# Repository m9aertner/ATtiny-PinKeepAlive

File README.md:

# ATtiny-PinKeepAlive

Flash in the PIN for my utility electricity meter via white LED, then keep the PIN active by flashing the LED briefly every 100 seconds.

In parallel, read INFO-DSS SML datagrams via IR diode input, decode for a number of OBIS codes and expose the received values via Modbus RTU over a serial line, in my case RS-485.

# Why?

The electricity power meter supplied by my local power company came mis-configured so there's no way to enable extended INFO-DSS IR datagrams permanently.
The respective menu item has been configured away. Thank you very much!

After PIN entry, the extended datagrams do appear, but only for 120 seconds. After that, the unit falls back to basic datagrams again, requiring another PIN entry. Alternatively, we just simulate some activity so that the 120 second window does not close. By repeated light signals, we're keeping the unit in "extended" mode, so to say.

Without the PIN, my meter emits 1.8.0 and 2.8.0 with kWh resolution only (xxx000 W) and does not emit instantaneous power at all. After PIN entry, all three values are emitted and with Watt granularity.

# Manual operation

A button is connected to a small microcontroller (ATtiny841) and makes a LED light up when pressed. The button is de-bounced so that a minimum LED "on" duration of around half a second is maintained. The button can be pressed for longer, extending the "on" period, which enables entry of "long" press light impulses.

In short, this function converts the error-prone manual flashing contraption to simple button presses.

# Automatic PIN entry

Upon reset, the microcontroller enters austomatic mode. It remains in automatic mode unless the button is pressed.
In automatic mode, the unit first
- emits a short flash to enter the display test page (all display segments activated)
- emits another short flash to proceed to the PIN entry page. With my meter, the display's 2nd line now shows '-0...-' and waits for the first digit.

Then, for each of the (four) digits of the PIN,
- a sequence of short flashes, each followed by a brief OFF pause is emitted, according to the digit value.
- Between digits, we need a pause of about 3-4 seconds. The meter detects this inactivity and switches to the next PIN position automatically.

As we do not have any feedback from the meter (neither IR nor visual) we can do nothing but try and wait for a similar amount of time. Note this cannot be super reliable. If the period is set too short, we're bumping up the current digit too much and if we wait for too long we can skip a digit, causing one or more spurious 0 digits.

The PIN is hard-coded in the source code / microcontroller. To define the PIN, copy file `meterpin-sample.h` to `meterpin.h` and adjust that copy to your PIN. Then build and upload. Setting the PIN to an empty string disables PIN entry, leaving only the Modbus-RTU function, see below.

# Keep Alive

After the automatic PIN entry or the last button press, the unit waits for 100 seconds, then emits a half-second LED flash and repeats. Pressing the button interrupts this waiting period and causes an immediate flash.

This short flash once in a while simulates some activity to the power meter so it does not ever reach the 120 second (2 minute) PIN timeout.

Consequently, the extended SML datagrams continue to be emitted. Mission accomplished.

# Repeat PIN entry

One reviewer suggested to enter the PIN again, regularly, to guard against unexpected meter resets and/or unexpected microcontroller resets.
So, after about 20 minutes, the unit now waits for a bit longer than the keep-alive period (130s, extended wait period), then blinks in the PIN again.

# What the heck?

I still have not found the reason why anybody would want to configure away the option to emit extended datagrams permanently. What's the purpose?!

While my unit is an [Easymeter Q3A](https://www.easymeter.com/downloads/products/zaehler/Q3A/BA_Q3A_V10.09_Rev19_2021-06-14.pdf), I believe there may be other types of meters with similar (stupid?) config options.

# Modbus RTU Details

The unit's address is fixed to 0x09. Function code 0x04 (Read Input Registers) is the only function code supported.

Four values are exposed. Each value is a 32bit value, readable through two consecutive registers.

| Address  | Content                                            | Unit | Data type               |
|----------|----------------------------------------------------|------|-------------------------|
| 256, 257 | Version number                                     |      | 32 bit unsigned integer |
| 258, 259 | 1-0:1.8.0 Positive active energy (A+) total        | Wh   | 32 bit unsigned integer |
| 260, 261 | 1-0:2.8.0 Negative active energy (A+) total        | Wh   | 32 bit unsigned integer |
| 262, 263 | 1-0:16.7.0 Sum active instantaneous power (A+ - A-)| W    | 32 bit signed integer   |

Example readout using "modpoll" (https://www.modbusdriver.com/modpoll.html):

    modpoll -t 3:int -a 9 -0 -r 256 -c 4 -i -1 -b 115200 -s 2 COM6

    modpoll -t 3:hex -a 9 -0 -r 258 -c 6    -1 -b 115200 -s 2 COM6

The SML decoder accepts 64-bit raw values internally, but after application of the "scaler" it is expected that the resulting
value fits into 32 bits. Indeed my unit always uses an 8-octet fixed-length zero-padded integer representation for all measurement
values:

    07 01 00 01 08 00 FF                1–0:1.8.0
    62 1e                               Unit
    52 03                               Scaler 10^3
    59 00 00 00 01 18 CB 47 05          0x118CB4705 <=> 4710942469, scaled to 471094 Wh, displayed on the unit as 471 kWh

# Hardware Design

I've prepared the schematics and a PCB using [KiCad 8.0.2](https://www.kicad.org/). Find respective project files under the [kicad/](kicad/) folder:
* [kicad/PinKeepAlive.kicad_pcb](kicad/PinKeepAlive.kicad_pcb)
* [kicad/PinKeepAlive.kicad_sch](kicad/PinKeepAlive.kicad_sch)

# Notes

- None of the values are critical, I believe.
- Use a small 100nF blocking condensator as C5, and position that near the MCU
- In the power supply section, I used 47uF/16V for C3, C4 which I had lying around. For the VBUS that I use a rating of 16V suffices, but please adapt when you supply with a higher voltage.
- The infrared phototransistor L14G3 is __ancient__ and comes from my forgotten parts bin. See https://wiki.volkszaehler.org/howto/simpler_ir_leser for other devices that people have found to work OK.
- By way of connector J6, you can also add a normal UART SmartMeterReader (e.g. [Amazon](https://www.amazon.de/bitShake-SmartMeterReader-UART-IR-Lesekopf/dp/B09XRC6VYW)). That's how I have it running currently. No need to populate U2, R4, R5, Q2 in this case, of course.
- The RS485 module can be obtained from AliExpress, Ebay, Amazon, or https://www.makershop.de/module/kommunikation-module/ttl-rs485-adapter/
- Same for the AMS1117-3V3 module. The 3-pin variant can be soldered easily and allows VBUS of up to 15V: https://www.berrybase.de/step-down-converter-5v-3-3v/800ma-mit-pin-header
- For the very short RS485 cable that I use, no 120 Ohm termination resistor is required. For longer cable lengths, be sure to terminate the RS485 bus at either end, usually by closing a solder bridge on the RS485 module.

# Caveats

- The LED needs to cause a light stream of at least 400lux at the receiver. I found that a random LED flashlight that I "deconstructed" for the purpose worked nicely: Originally driven by 3x AAA, the LED seems to be OK with being driven by nearly 5V (at 100mA). I ended up using a constant-current circuit (http://www.loosweb.de/constant_current_sources/doc/en/index.html point 8) where the current is determined by the 50Ohms resistor (2x 100Ohms parallel is what I had). The flashing I get this way is strong enough for my meter.
- (Update) Now that my meter emits long datagrams without any further ado, I converted the LED part to a "heartbeat" by configuring away the PIN and setting a 60 second keep-alive interval. The main objective now is to use the RS485 portion.
- The timing of this whole PIN entry scheme is not overly critical, but certainly not fool-proof either. After all, it's intended for manual operation. Especially, the inter-digit delays may give you a problem. In this case, please adjust `DIGIT_GAP2_TICKS` in code and re-try.
- If your meter happens to __not__ have a sticker preventing access to the MSB-DSS (IR transmitter/receiver, lucky you!), you want to check there first, as the MSB-DSS may well emit extended datagrams irrspective of PIN entry status - that is, even without a PIN!
- Why ATtiny841? Well, that was the nearest unit I happened to find on my workbench. And it's got two hardware serial ports, which I use now to read the SML and forward that via wired RS485. Of course, for the basic LED flash function any Arduino-like microcontroller
with some form of periodic interrupt should work.
- Note that during the last seconds of the extended wait period, plus the seconds it takes to re-enter the PIN, the meter will send out reduced datagrams again. Please ping me when you know a way around this.
- Please note that Modbus-RTU **requires** eleven bit times per character on the line. This means that when __not__ using any parity one must use **two** stop bits (start bit, 8 character bits, 2 stop bits == 11 bits). While some tools worked with just one stop bit  (modpoll), I found that others do not! Yes, especially PyModbus did rightfully **not** work unless the unit was configured to two stop bits. And that's critical as my HomeAssistant Modbus integration uses PyModbus under the covers.

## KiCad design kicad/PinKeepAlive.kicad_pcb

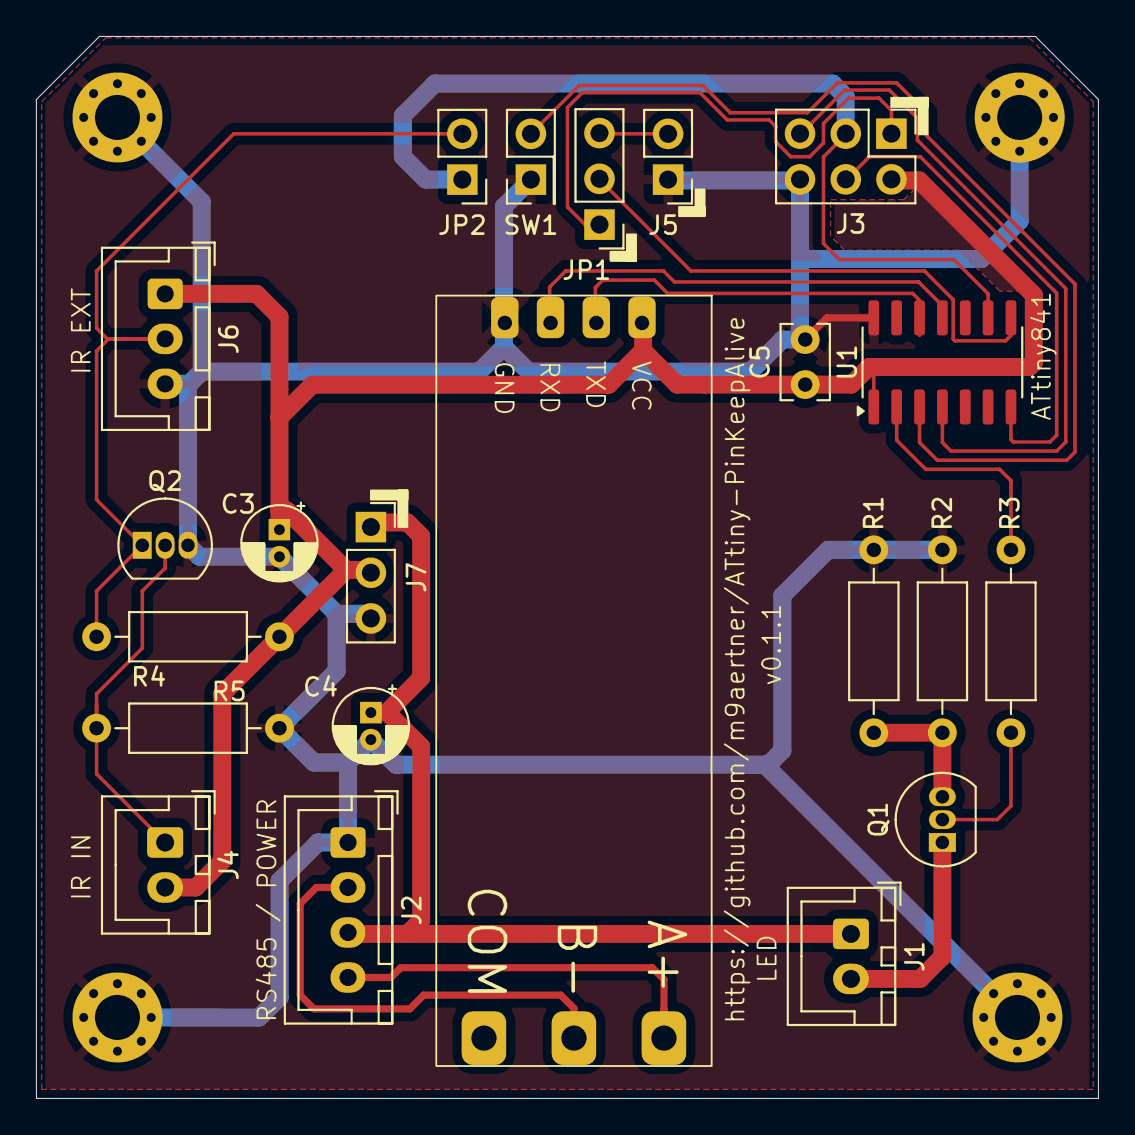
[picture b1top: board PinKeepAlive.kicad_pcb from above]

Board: 2 copper layers, 59.0 x 59.0 mm, 26 parts (0 on the bottom side), 20 nets.

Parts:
C3, C4: 47µ; CP_Radial_D4.0mm_P1.50mm
C5: C; C_Rect_L4.0mm_W2.5mm_P2.50mm
H1, H2, H3, H4: MountingHole_Pad; MountingHole_2.5mm_Pad_Via
J1: LED1; JST_XH_B2B-XH-A_1x02_P2.50mm_Vertical
J2: XLR4/RS485; JST_XH_B4B-XH-A_1x04_P2.50mm_Vertical
J3: AVR-ISP-6; PinHeader_2x03_P2.54mm_Vertical
J4: INFO-DSS IR; JST_XH_B2B-XH-A_1x02_P2.50mm_Vertical
J5: DBG Serial; PinHeader_1x02_P2.54mm_Vertical
J6: INFO-DSS Ext Rcvr; JST_XH_B3B-XH-A_1x03_P2.50mm_Vertical
J7: Conn_01x03_Socket; PinSocket_1x03_P2.54mm_Vertical
JP1: 1-2 PRG 2-3 DBG; PinHeader_1x03_P2.54mm_Vertical
JP2: INFO-DSS Disconnect; PinHeader_1x02_P2.54mm_Vertical
Q1, Q2: BC547; TO-92_Inline
R1, R2: 100R; R_Axial_DIN0207_L6.3mm_D2.5mm_P10.16mm_Horizontal
R3: 470R; R_Axial_DIN0207_L6.3mm_D2.5mm_P10.16mm_Horizontal
R4, R5: 10K; R_Axial_DIN0207_L6.3mm_D2.5mm_P10.16mm_Horizontal
SW1: PinHeader_2x01_P2.54mm_Vertical
U1: ATtiny841-SS; SOIC-14_3.9x8.7mm_P1.27mm
U4: RS485toTTL-THT

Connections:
+3V3: C3.1, C5.1, J3.2 (VCC), J4.2, J6.1, J7.2, R4.1, U1.1 (VCC), U4.1 (VCC)
GND: C3.2, C4.2, C5.2, H1.1, H2.1, H3.1, H4.1, J2.1, J3.6 (GND), J5.1, J6.3, J7.3, Q2.3 (E), R1.2, R2.2, R5.2, SW1.1, U1.14 (GND), U4.4 (GND)
unnamed: J1.2, Q1.1 (C)
unnamed: J3.1 (MISO), JP1.1 (A)
unnamed: J3.4 (MOSI), U1.7 (PA6)
unnamed: J3.3 (SCK), JP2.1 (A), U1.9 (PA4)
unnamed: J3.5 (~RST), U1.4 (~RESET/PB3)
unnamed: J4.1, Q2.2 (B), R5.1
unnamed: J5.2, JP1.3 (B)
unnamed: J6.2, JP2.2 (B), Q2.1 (C), R4.2
unnamed: JP1.2 (C), U1.8 (PA5)
unnamed: Q1.2 (B), R3.1
unnamed: Q1.3 (E), R1.1, R2.1
unnamed: U1.12 (PA1), U4.2 (TXD)
unnamed: U1.11 (PA2), U4.3 (RXD)
unnamed: R3.2, U1.2 (XTAL1/PB0)
unnamed: SW1.2, U1.3 (XTAL2/PB1)
unnamed: J2.4, U4.7 (A+)
unnamed: J2.2, U4.6 (B-)
VBUS: C4.1, J1.1, J2.3, J7.1

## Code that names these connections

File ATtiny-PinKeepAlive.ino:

/*
   ATtiny-PinKeepAlive
   - Chip: ATtiny841
   - Clock: 8MHz internal

   Hardware:
   - PB0       White LED via BC557 PNP transistor, with 4K7 resistor to base, active LOW
               To use an NPN transistor (active HIGH), define LED_ON and LED_OFF accordingly in meterpin.h
   - PB1       Push button against GND
   - PA1       TXD0 USART0 RS-485, physical pin 12
   - PA2       RXD0 USART0 RS-485, physical pin 11
   - PA5       TXD1 USART1 DEBUG, physical pin 8, used with __DEBUG__ = 1 (may cause timing ModBus RTU problems)
   - PA4       RXD1 USART1 INFO-DSS Infrared (idle high), physical pin 9

   v0.5        May 2024
*/

#include <Arduino.h>
#include "PinKeepAlive.h"
#include "ExposeToModbus.h"
#include "ReadFromInfoDSS.h"

#ifdef PINMAPPING_CCW
#error "Sketch was written for clockwise pin mapping!"
#endif

volatile static bool ticked = false;

static ObisValues obisValues = ObisValues();
static TinySMLDecoder tinySMLDecoder = TinySMLDecoder(&obisValues);

// Called every 100ms
ISR(TIMER1_COMPA_vect)
{
  ticked = true;
}

// Reset ticked to false, return true if it was ticked.
bool resetTicked()
{
  bool r = ticked;
  ticked = false;
  return r;
}

void setup()
{
  setupPinKeepAlive();
  pushPinEntry();
  setupModbus(&obisValues);
  setupInfoDSS(&tinySMLDecoder);
}

void loop()
{
  if (resetTicked())
  {
    onTickPinKeepAlive();
  }

  onTickModbus();
  onTickInfoDSS();
}

// END

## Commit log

2024-02-10 Automatic PIN entry
2024-02-10 Manual PIN entry only, flash length adjusted
2024-02-10 Initial commit, manual PIN entry only
2024-02-12 Automatic PIN re-entry
2024-02-18 Minor: allow NPN transistor, active HIGH
2024-05-06 Exposure via RS-485 Modbus-RTU
2024-05-09 Schematic
2024-05-09 Added module links.
2024-05-24 KiCad PCB
2024-05-26 Adding post-prototype installation photo. Working great so far!
